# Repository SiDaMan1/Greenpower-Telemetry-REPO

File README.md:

# Greenpower Telemetry

A live telemetry system built for the Greenpower race vehicle. Sensors on the car — speed, battery/motor voltage, current, temperature, motor & wheel RPM, IMU orientation and G-forces, GPS, ESC state, LoRa link quality — stream off the car in real time, get picked up by a base-station receiver, and show up on a public web dashboard within a fraction of a second. Every packet is also saved, so past runs and test sessions can be reviewed and exported later, not just watched live.

```
Vehicle (greenpower_sender) ──LoRa──▶ greenpower_receiver ──USB──▶ receiver_agent ──▶ telemetry_web (dashboard)
                             └─ESP-NOW──▶ steering_wheel_display
```

- **`greenpower_sender`** — firmware on the car itself, reads every sensor and transmits over both LoRa (long-range, to the pits) and ESP-NOW (short-range, straight to the steering wheel).
- **`greenpower_receiver`** — a base-station ESP32 that catches the LoRa packets and relays them over USB.
- **`receiver_agent`** — a small background app on a laptop plugged into the receiver. It watches for the device, asks before forwarding (nothing goes live without a person clicking "Yes"), and pushes packets to the dashboard.
- **`telemetry_web`** — the dashboard itself: live numbers and charts, GPS raceline on a real map, session history with CSV export, installable as a mobile app.
- **`steering_wheel_display`** — the driver's own live readout, wired straight into the car's ESP-NOW link, no dependency on the receiver/agent/internet chain at all.

---

## 🏁 Live Dashboard

**[ascteracingmonitor.com →](https://ascteracingmonitor.com/)**

Open it anytime to see whatever the car is currently transmitting — speed, power, temperatures, RPM, ESC status, IMU data, live GPS raceline on satellite imagery, and LoRa link quality, all updating several times a second. When nothing is actively forwarding it just shows offline, not stale numbers pretending to be current.

A few things worth knowing if you're using it, not just building it:
- **Time range toggle** (top of the page) — switch the live charts between 1/5/15/30 minutes or the whole session, not just a fixed short window.
- **Sessions tab** — every run gets grouped automatically and stays browsable afterward, with a one-click CSV export of the full packet history.
- **Multi tab** — overlay several metrics normalized onto one chart, useful for spotting correlations (e.g. current spikes vs. RPM dips).
- **Install it as an app** — on a phone, use your browser's "Add to Home Screen"/"Install" option for a full-screen, no-browser-chrome experience with its own icon.

## 📥 Get telemetry flowing to the dashboard

If you just need the car's data reaching the dashboard, you don't need this whole repo — only the **receiver agent**, running on whatever laptop the base-station receiver is plugged into.

1. Click the button above → downloads `GreenpowerAgentSetup.msi` (a real Windows installer, ~500 KB)
2. Run it and click through the setup wizard

No unzipping, no `.bat` files — it's a proper installer: Start Menu shortcut, entry in Add/Remove Programs (Settings → Apps → Installed apps → Uninstall), no admin rights needed (installs to your own user folder). It still installs its own dependencies, config is already baked in, and it registers itself to auto-start at login (plus a small tray icon so you can tell it's running). Requires [Node.js](https://nodejs.org) (LTS) already installed. After setup, day-to-day use is just: plug in the receiver, click **Yes** on the notification that pops up asking permission to forward. Unplug/replug always re-asks — it never silently starts forwarding on its own.

`.msi`, not the more common `.exe` — deliberate, not a typo. An earlier `.exe` build (Inno Setup) worked fine generally but got hard-blocked by Windows on Intune-managed/corporate devices (a Defender rule that specifically targets raw executables); an MSI sidesteps that since it isn't that kind of file. See `receiver_agent/CLAUDE.md` if you're curious about the full story.

The same download button also lives on the dashboard itself (top-right, desktop) for anyone who lands there first — it opens a short confirmation dialog first, since this is now a real installer someone's about to run, not an inert zip.

More detail, including what the consent prompt is actually protecting against: [`receiver_agent/README.md`](receiver_agent/README.md)

---

## Project map

| Folder | What it is |
|---|---|
| [`greenpower_sender`](greenpower_sender) | Firmware on the vehicle (ESP32-S3) — reads sensors, transmits over LoRa + ESP-NOW |
| [`greenpower_receiver`](greenpower_receiver) | Firmware on a base-station ESP32 — receives LoRa, relays JSON over USB serial |
| [`receiver_agent`](receiver_agent) | Node.js background agent (runs on a laptop) — watches for the receiver over USB, asks before forwarding, relays to the dashboard, tray icon |
| [`telemetry_web`](telemetry_web) | The dashboard itself (Node/Express + Postgres), deployed on Railway — live view, session history, mobile PWA |
| [`steering_wheel_display`](steering_wheel_display) | Firmware for the steering wheel's own live display (ESP-NOW receiver) |
| [`mock_sender`](mock_sender) | Fake sender for testing the display/dashboard without the real car |
| [`esc controller`](esc%20controller) | Firmware for the motor controller (ESP32 WROOM-32), talks to the sender over UART |

Each folder has its own `CLAUDE.md` with the real technical detail — hardware wiring, pinouts, protocol formats, known gotchas. This README is the map for a human reader; those files are the AI-assistant-facing equivalent, kept in sync with whatever's actually true in the code.

## Running your own copy

Every piece here is meant to work as a drop-in replacement for testing without the real car: `mock_sender` speaks the exact same LoRa/ESP-NOW packet formats as `greenpower_sender`, so a receiver or steering-wheel display can't tell the difference — and `telemetry_web` itself has a built-in **Test Mode** toggle (top of the dashboard) that feeds realistic sample data through the live charts with no hardware at all, for trying out the UI. See each folder's own README/CLAUDE.md for the specifics of setting that piece up.

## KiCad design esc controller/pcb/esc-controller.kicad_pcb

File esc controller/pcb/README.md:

# ESC Controller PCB — rev D

A carrier board for the `throttle_controller` sketch. The ESP32 DevKit V1 (30-pin)
plugs into two female header strips. The SSD1306 OLED solders **flush to the board**
through four plated holes. Everything else leaves the board on **1 × 2 mm solder
pads** for flying leads.

**One component on the whole board: R1, a 4k7 pull-down on the ESC signal.**

Open `esc-controller.kicad_pro` in KiCad 7 or newer.

```
Board        73 × 60 mm, 2 layer, 1.6 mm
Copper       1 oz, GND pour both sides
Tracks       0.25 mm signal / 0.5 mm power
Vias         0.8 mm pad / 0.4 mm drill
Min clear.   0.3 mm  (well inside every cheap fab's limits)
DRC          0 violations, 0 unconnected pads, 0 footprint errors
```

### What changed from rev C

Area-optimised: **98 × 62 mm → 73 × 60 mm**, a 28% smaller board (6076 → 4380 mm²)
and 25 mm narrower. Nothing electrical changed — same nets, same pads, same parts.

- Three tight columns instead of loose ones: wire pads at the left edge, the
  DevKit socket, then the OLED with the UART pads tucked into the dead space
  underneath it
- **R1 now stands vertically** (2.54 mm pitch, one lead bent down) so it fits the
  3 mm lane between the pad labels and the socket. Same 4k7 resistor, just mounted
  on end — bend one lead back alongside the body before you fit it
- 5V IN moved to the left column, next to the VIN pin it feeds
- Smaller silkscreen text and tighter pad-group spacing throughout
- The two modules now take up 51% of the board area; the rest is wire pads,
  mounting holes and edge margin

### What changed from rev B

- ECO and SPORT are no longer two separate 2-pad groups. They're now **one 3-pad
  MODE SW group** — `ECO / COM / SPORT` — for a single 3-position switch
- Connectors renumbered again: TRIGGER is **J5**, UART OUT is **J6**, 5V IN is **J7**

### What changed from rev A

- All pull-ups, filter caps, bulk cap, power LED and its resistor removed
- R1 (4k7) rewired from series to a **pull-down**, ESC signal to ground
- OLED changed to four plated holes for flush mounting
- Board grew 95 → 98 mm wide

---

## The mode switch

`MODE SW` (J4) takes one **SP3T / 3-position** switch. Wire the switch's common
terminal — the centre pin on almost every slide switch — to the middle pad, and the
two outer terminals to `ECO` and `SPORT`. Because GND sits between the two signals,
the switch's three pins map straight across without any wire crossing over another.

| Switch position | ECO pin | SPORT pin | Mode |
|---|---|---|---|
| One end | pulled low | high | ECO |
| **Centre** | high | high | **NORMAL** |
| Other end | high | pulled low | SPORT |

That falls out of the firmware as written: both inputs are active-low, and with
neither pulled down it lands on NORMAL. There's no way for both to be low at once
with a single switch, so the "ECO wins if both are low" tie-break in the sketch
simply never fires — harmless to leave in.

Which end gives you ECO and which gives SPORT is just which way round you solder
the two outer wires. Swap them if it ends up backwards.

---

## What R1 does

GPIO25 goes straight to the `ESC OUT / SIG` pad. R1 sits across that signal to
ground.

The ESP32's pins are high-impedance during reset and for the first moments of
boot — nothing is driving them. Without a pull-down, the ESC input floats during
that window and can read as anything, which is how a car twitches or lurches when
you power it up. R1 holds the line at 0 V until the firmware takes over. It also
holds the ESC off if the signal wire ever comes loose.

At 3.3 V it draws 0.7 mA when GPIO25 is high — nothing next to what the pin can
source, and negligible against the 31 kHz switching.

**One thing to watch:** if your ESC's signal input has its own internal pull-up,
R1 forms a voltage divider with it and the idle level won't reach 0 V. If the
throttle won't fully close, or the ESC sees a standing signal with the ESP32
unplugged, that's the cause — swap R1 for 10 kΩ or higher. The pads take any
value; it's a one-part change, no board revision needed.

---

## ⚠️ Two things to check before you order

**1. The DevKit row pitch.** The socket assumes **25.4 mm (1.0") between the two
pin rows** — standard for a 30-pin DOIT DevKit V1, but some clones are 22.86 mm
(0.9"). Measure yours, centre-of-pin to centre-of-pin across the rows. If it's
different, change `ROW_SPACING` in `generator/design.py` and re-run
`generator/build.py`. Nothing else has to change.

**2. Where the OLED's pin row sits.** The four holes are on 2.54 mm pitch — that
part is universal. I've placed them **centred on the top edge** of the module and
drawn a 27.3 × 27.8 mm body outline on the silkscreen as a guide. If your module's
header is offset rather than centred, the module will just sit a few mm off from
the printed outline — the board area underneath is completely clear, so nothing
collides. Cosmetic only.

Pin order is **GND, VCC, SCL, SDA** left to right, viewed from above with the
screen facing up. Every hole is labelled on the silkscreen — check them against
your module before you solder, because getting GND and VCC swapped will kill the
display.

---

## Wiring — what goes on which pad

All solder pads are on the top layer, labelled on the silkscreen.

### Left edge

| Group | Pad | Net | Connect to | ESP32 |
|---|---|---|---|---|
| **POT** (J2) | 3V3 | +3V3 | pot terminal 1 | — |
| | WIPER | POT_W | pot wiper | GPIO34 |
| | GND | GND | pot terminal 3 | — |
| **ESC OUT** (J3) | SIG | ESC_SIG | ESC signal wire | GPIO25 direct, R1 pulls it down |
| | GND | GND | ESC ground | — |
| **MODE SW** (J4) | ECO | ECO | switch outer terminal | GPIO27 |
| | COM | GND | switch **common** (centre pin) | — |
| | SPORT | SPORT | switch other outer terminal | GPIO14 |
| **TRIGGER** (J5) | SW | TRIG | trigger switch, one side | GPIO13 |
| | GND | GND | trigger switch, other side | — |
| **5V IN** (J7) | 5V | +5V | BEC / buck output — **optional** | VIN |
| | GND | GND | BEC ground | — |

The trigger and both mode inputs are active-low and rely on the **ESP32's internal
pull-ups** — make sure the sketch declares these pins as `INPUT_PULLUP`, not plain
`INPUT`, or they'll float.

### Right side and OLED

| Group | Pad | Net | Connect to | ESP32 |
|---|---|---|---|---|
| **OLED** (J1) | GND, VCC, SCL, SDA | — | module solders flush, pins down | GPIO22 = SCL, GPIO21 = SDA |
| **UART OUT** (J6, under the OLED) | TX | UART_TX | display_receiver RX | GPIO17 |
| | RX | UART_RX | display_receiver TX | GPIO16 |
| | GND | GND | display_receiver GND | — |

**J7 is optional.** You're on USB power, so leave it unpopulated. It's there so the
board can run standalone later without a redesign. If you do use it, **don't leave
USB plugged in at the same time** — the DevKit V1 has no isolation between the USB
5V rail and VIN.

---

## Bill of materials

| Ref | Value | Package | Qty | Notes |
|---|---|---|---|---|
| U1 | 1×15 female header, 2.54 mm | THT | 2 | Cut from a 40-pin strip. The DevKit sits in these. |
| R1 | 4.7 kΩ | axial, **mounted vertically**, 2.54 mm | 1 | Pull-down, ESC signal to GND |
| H1–H4 | M3 | 3.2 mm hole | 4 | Mounting |

That's the entire BOM. J1 is four plated holes — the OLED module's own pins go
through them, no header needed. J2–J7 are bare solder pads. The mode switch,
trigger, pot and ESC are all off-board on flying leads.

---

## Assembly order

1. **R1** first. It mounts **standing up**: bend one lead 180° back along the body
   so both leads come out of the same end, 2.54 mm apart. Either way round; a
   resistor isn't polarised.
2. **The two 1×15 female strips for U1.** Plug the DevKit into them while you
   solder so the rows end up parallel, but keep it unpowered.
3. **The OLED.** Its pin header goes through J1 from the top with the module lying
   flat on the board; solder underneath and trim the pins flush. Check the four
   silkscreen labels against the module first.
4. **Flying leads** to the solder pads. Tin the pad, tin the wire, lay the wire flat
   on the pad and reflow. Add a dab of hot glue after testing — an unsupported
   soldered wire will fatigue and snap in a race car.

The OLED sits directly on the board, so the copper under it is bare board and
solder mask only — no components, nothing to short against.

---

## Manufacturing

`gerbers.zip` uploads to JLCPCB / PCBWay / OSHPark as-is (Gerber X2 + Excellon
drill, mm). Default settings: 2 layer, 1.6 mm, HASL, any colour. At 73 × 60 mm
it's comfortably inside the 100 × 100 mm price break — roughly $2–5 for five
boards plus shipping.

### If you need it smaller still

Two things set the size, and both are choices rather than physics:

- **The four M3 mounting holes** cost roughly 7 mm of board at each corner. Two
  holes instead of four, or M2.5 instead of M3, would let the board come in
  another 4–5 mm each way.
- **The layout is three columns.** Stacking the OLED *below* the DevKit instead
  of beside it gives a long, narrow board (about 45 × 85 mm) — slightly less area,
  but a much less square shape. Better if it mounts along a dash rail, worse if
  it goes in a box.

Say which you'd prefer and it's a placement change in `design.py`, not a redesign.

---

## Regenerating

The project is generated from source, so changes stay consistent:

```
cd generator
python3 build.py      # places, routes, checks clearances, writes the .kicad_pcb
python3 gen_sch.py    # writes the .kicad_sch and .kicad_pro
```

`design.py` holds everything worth changing — board size, `ROW_SPACING`, placement,
the pad groups and the netlist. `router.py` is a two-layer maze router with
clearance checking; `build.py` places, routes, then runs its own geometric
clearance and connectivity checks before writing the board. Needs `numpy`.

---

## Verification done on this design

- KiCad's own DRC: **0 violations, 0 unconnected pads, 0 footprint errors**
  (see `drc_report.txt`)
- Independent geometric clearance check: 0 pairs closer than 0.20 mm
- Independent connectivity check: every net's pads joined by copper
- Schematic netlist exported and diffed against the PCB netlist — **all 12 nets
  match exactly**, same pads on the same nets, same footprints
- `ECO` confirmed as J4 pad 1 → U1 pin 10 (GPIO27), `SPORT` as J4 pad 3 → U1
  pin 11 (GPIO14), and J4 pad 2 on GND
- `ESC_SIG` confirmed to carry exactly U1 pin 8 (GPIO25), J3 pad 1 and R1 pad 1,
  with R1 pad 2 landing in the ground pour
- Every GPIO cross-checked against `SYSTEM_INFO.md`, and every pin confirmed to
  exist on the 30-pin DevKit V1
- Thermal relief checked: every ground through-hole pad gets at least two spokes
  into the pour, so no pad hangs off the plane by a single thin bridge

The two things software can't check for you are the 25.4 mm row pitch and your
OLED's pin order. Both are one measurement each.

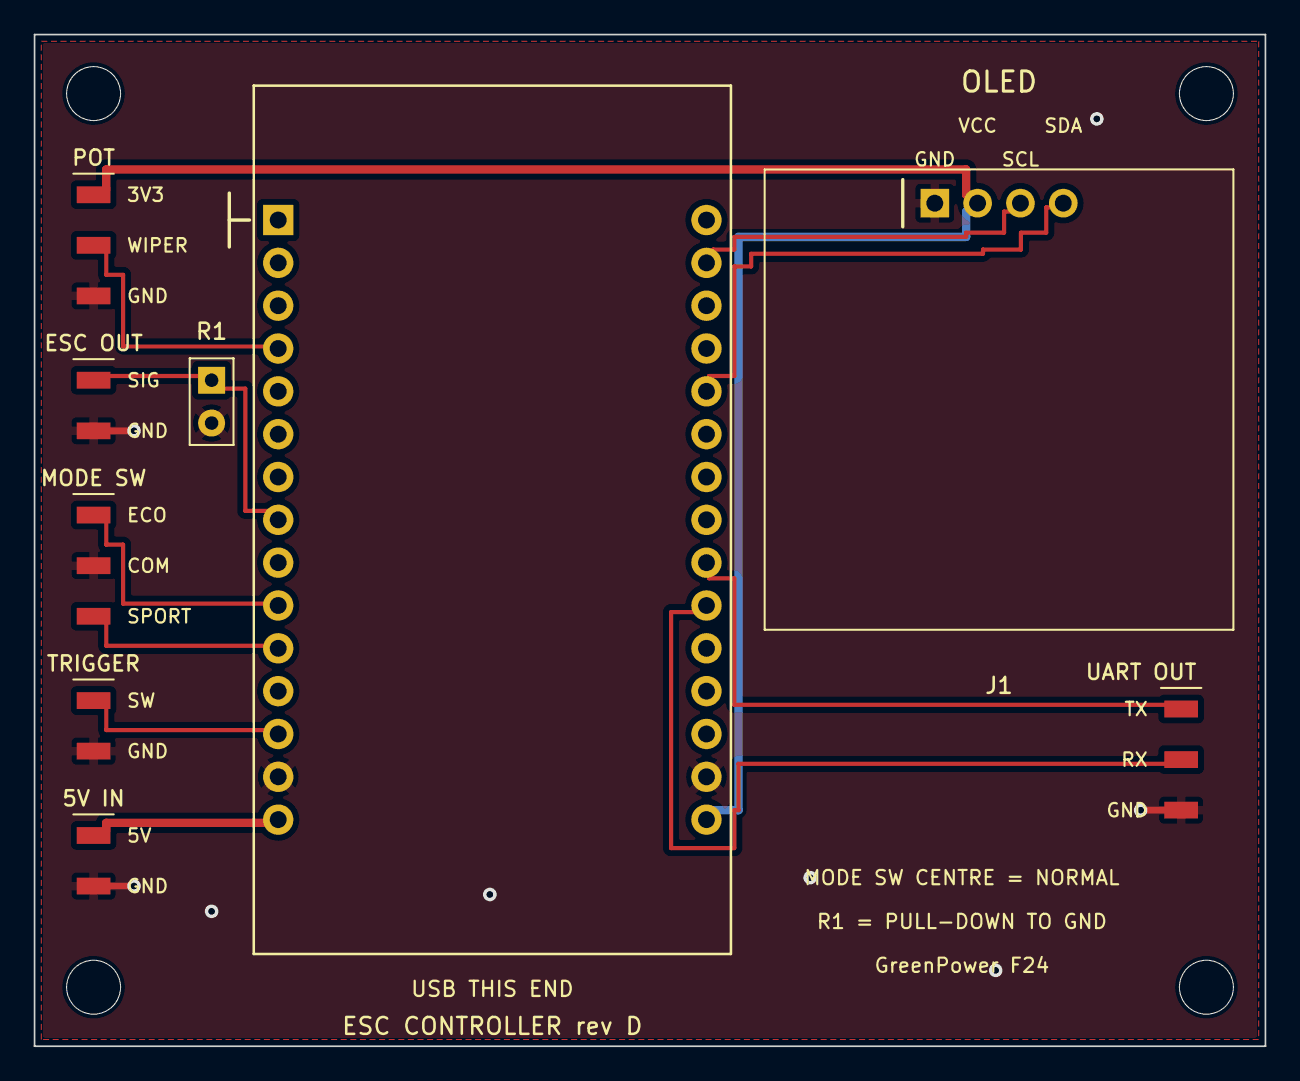
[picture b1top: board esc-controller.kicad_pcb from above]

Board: 2 copper layers, 73.0 x 60.0 mm, 13 parts (0 on the bottom side), 12 nets.

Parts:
H1, H2, H3, H4: MountingHole_M3; MountingHole_3.2mm_M3
J1: SSD1306_0.96in; OLED_SSD1306_096_FLUSH_1x4
J2: WirePads; SOLDERPAD_POT_3P
J3: WirePads; SOLDERPAD_ESC_OUT_2P
J4: WirePads; SOLDERPAD_MODE_SW_3P
J5: WirePads; SOLDERPAD_TRIGGER_2P
J6: WirePads; SOLDERPAD_UART_OUT_3P
J7: WirePads; SOLDERPAD_5V_IN_2P
R1: 4k7; Resistor_THT_Axial_P2.54mm_Vertical
U1: ESP32-DevKitV1-30p; ESP32_DEVKITV1_30P_SOCKET

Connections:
+3V3: J1.2, J2.1, U1.30
+5V: J7.1, U1.15
ECO: J4.1, U1.10
ESC_SIG: J3.1, R1.1, U1.8
GND: J1.1, J2.3, J3.2, J4.2, J5.2, J6.3, J7.2, R1.2, U1.14, U1.29
POT_W: J2.2, U1.4
SCL: J1.3, U1.17
SDA: J1.4, U1.20
SPORT: J4.3, U1.11
TRIG: J5.1, U1.13
UART_RX: J6.2, U1.25
UART_TX: J6.1, U1.24

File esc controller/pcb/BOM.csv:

Ref,Value,Footprint,Qty,Description
U1,1x15 female header 2.54mm,esc:ESP32_DEVKITV1_30P_SOCKET,2,Socket strips for ESP32 DevKit V1 30-pin (cut from 40-pin strip)
R1,4k7,esc:Resistor_THT_Axial_P2.54mm_Vertical,1,Pull-down from ESC signal to GND - MOUNTED VERTICALLY (bend one lead back along the body)
H1-H4,M3,esc:MountingHole_3.2mm_M3,4,Mounting holes
J1,OLED holes,esc:OLED_SSD1306_096_FLUSH_1x4,1,4 plated holes 2.54mm - SSD1306 solders flush - GND VCC SCL SDA
J2,POT pads,esc:SOLDERPAD_POT_3P,1,Solder pads 1x2mm: 3V3 / WIPER / GND
J3,ESC OUT pads,esc:SOLDERPAD_ESC_OUT_2P,1,Solder pads 1x2mm: SIG / GND
J4,MODE SW pads,esc:SOLDERPAD_MODE_SW_3P,1,Solder pads 1x2mm: ECO / COM / SPORT - one 3-position switch, common to COM
J5,TRIGGER pads,esc:SOLDERPAD_TRIGGER_2P,1,Solder pads 1x2mm: SW / GND
J6,UART OUT pads,esc:SOLDERPAD_UART_OUT_3P,1,Solder pads 1x2mm: TX / RX / GND
J7,5V IN pads,esc:SOLDERPAD_5V_IN_2P,1,Solder pads 1x2mm: 5V / GND - OPTIONAL do not fit for USB power

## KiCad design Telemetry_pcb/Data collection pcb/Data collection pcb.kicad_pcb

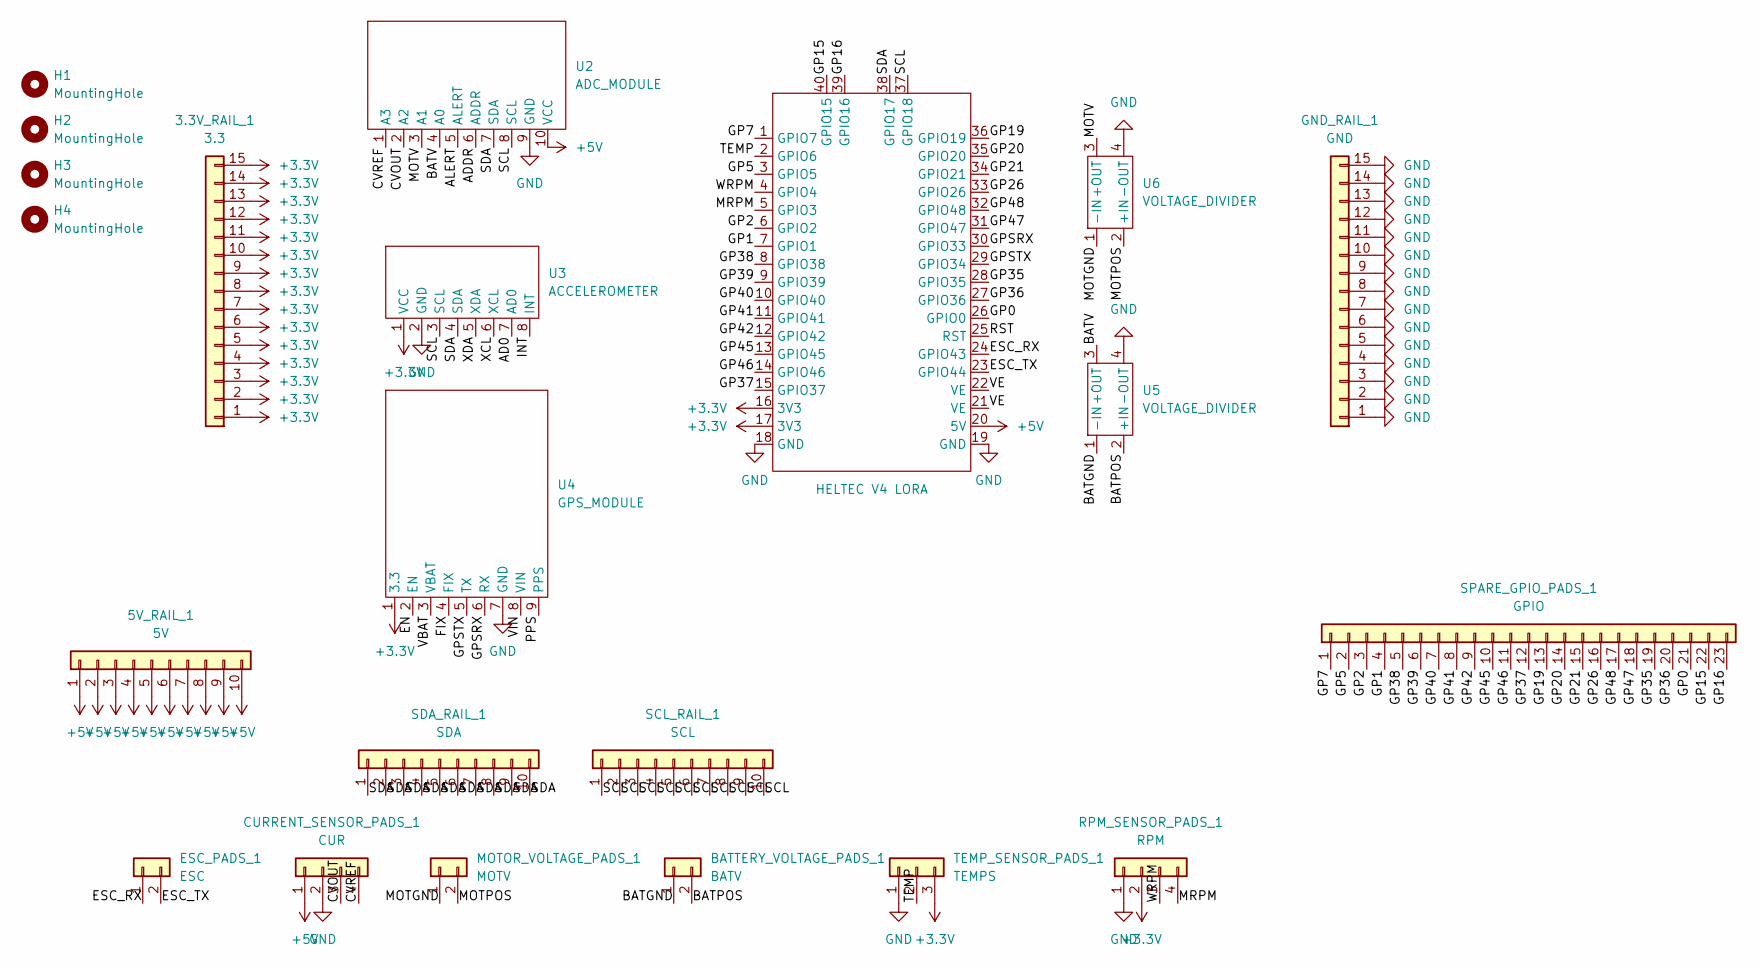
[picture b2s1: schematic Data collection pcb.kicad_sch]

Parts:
3.3V_RAIL_1: 3.3; 1X15 PADS
5V_RAIL_1: 5V; 1X10 PADS
BATTERY_VOLTAGE_PADS_1: BATV; 1X02 PADS
CURRENT_SENSOR_PADS_1: CUR; 1X04 PADS
ESC_PADS_1: ESC; 1X02 PADS
GND_RAIL_1: GND; 1X15 PADS
H1, H2, H3, H4: MountingHole; MountingHole_3.2mm_M3
MOTOR_VOLTAGE_PADS_1: MOTV; 1X02 PADS
RPM_SENSOR_PADS_1: RPM; 1X04 PADS
SCL_RAIL_1: SCL; 1X10 PADS
SDA_RAIL_1: SDA; 1X10 PADS
SPARE_GPIO_PADS_1: GPIO; 1X23 PADS
TEMP_SENSOR_PADS_1: TEMPS; 1X03 PADS
U1: HELTEC V4 LORA; HELTEC V4
U2: ADC_MODULE
U3: ACCELEROMETER
U4: GPS_MODULE
U5, U6: VOLTAGE_DIVIDER

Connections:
+3.3V: 3.3V_RAIL_1.1, 3.3V_RAIL_1.2, 3.3V_RAIL_1.3, 3.3V_RAIL_1.4, 3.3V_RAIL_1.5, 3.3V_RAIL_1.6, 3.3V_RAIL_1.7, 3.3V_RAIL_1.8, 3.3V_RAIL_1.9, 3.3V_RAIL_1.10, 3.3V_RAIL_1.11, 3.3V_RAIL_1.12, 3.3V_RAIL_1.13, 3.3V_RAIL_1.14, 3.3V_RAIL_1.15, RPM_SENSOR_PADS_1.2, TEMP_SENSOR_PADS_1.3, U1.16 (3V3), U1.17 (3V3), U3.1 (VCC), U4.1 (3.3); also elsewhere on the board
+5V: 5V_RAIL_1.1, 5V_RAIL_1.2, 5V_RAIL_1.3, 5V_RAIL_1.4, 5V_RAIL_1.5, 5V_RAIL_1.6, 5V_RAIL_1.7, 5V_RAIL_1.8, 5V_RAIL_1.9, 5V_RAIL_1.10, CURRENT_SENSOR_PADS_1.1, U1.20 (5V), U2.10 (VCC)
/AD0: U3.7 (AD0)
/ADDR: U2.6 (ADDR)
/ALERT: U2.5 (ALERT)
/BATGND: BATTERY_VOLTAGE_PADS_1.1, U5.1 (-IN)
/BATPOS: BATTERY_VOLTAGE_PADS_1.2, U5.2 (+IN)
/BATV: U2.4 (A0), U5.3 (+OUT)
/CVOUT: CURRENT_SENSOR_PADS_1.3, U2.2 (A2)
/CVREF: CURRENT_SENSOR_PADS_1.4, U2.1 (A3)
/EN: U4.2 (EN)
/ESC_RX: ESC_PADS_1.1, U1.24 (GPIO43)
/ESC_TX: ESC_PADS_1.2, U1.23 (GPIO44)
/FIX: U4.4 (FIX)
/GP0: SPARE_GPIO_PADS_1.21, U1.26 (GPIO0)
/GP1: SPARE_GPIO_PADS_1.4, U1.7 (GPIO1)
/GP2: SPARE_GPIO_PADS_1.3, U1.6 (GPIO2)
/GP5: SPARE_GPIO_PADS_1.2, U1.3 (GPIO5); also elsewhere on the board
/GP7: SPARE_GPIO_PADS_1.1, U1.1 (GPIO7); also elsewhere on the board
/GP15: SPARE_GPIO_PADS_1.22, U1.40 (GPIO15)
/GP16: SPARE_GPIO_PADS_1.23, U1.39 (GPIO16)
/GP19: SPARE_GPIO_PADS_1.13, U1.36 (GPIO19)
/GP20: SPARE_GPIO_PADS_1.14, U1.35 (GPIO20)
/GP21: SPARE_GPIO_PADS_1.15, U1.34 (GPIO21)
/GP26: SPARE_GPIO_PADS_1.16, U1.33 (GPIO26)
/GP35: SPARE_GPIO_PADS_1.19, U1.28 (GPIO35)
/GP36: SPARE_GPIO_PADS_1.20, U1.27 (GPIO36)
/GP37: SPARE_GPIO_PADS_1.12, U1.15 (GPIO37)
/GP38: SPARE_GPIO_PADS_1.5, U1.8 (GPIO38)
/GP39: SPARE_GPIO_PADS_1.6, U1.9 (GPIO39)
/GP40: SPARE_GPIO_PADS_1.7, U1.10 (GPIO40)
/GP41: SPARE_GPIO_PADS_1.8, U1.11 (GPIO41)
/GP42: SPARE_GPIO_PADS_1.9, U1.12 (GPIO42)
/GP45: SPARE_GPIO_PADS_1.10, U1.13 (GPIO45)
/GP46: SPARE_GPIO_PADS_1.11, U1.14 (GPIO46)
/GP47: SPARE_GPIO_PADS_1.18, U1.31 (GPIO47); also elsewhere on the board
/GP48: SPARE_GPIO_PADS_1.17, U1.32 (GPIO48); also elsewhere on the board
/GPSRX: U1.30 (GPIO33), U4.6 (RX)
/GPSTX: U1.29 (GPIO34), U4.5 (TX)
/INT: U3.8 (INT)
/MOTGND: MOTOR_VOLTAGE_PADS_1.1, U6.1 (-IN)
/MOTPOS: MOTOR_VOLTAGE_PADS_1.2, U6.2 (+IN)
/MOTV: U2.3 (A1), U6.3 (+OUT)
/MRPM: RPM_SENSOR_PADS_1.4, U1.5 (GPIO3)
/PPS: U4.9 (PPS)
/RST: U1.25 (RST)
/SCL: SCL_RAIL_1.1, SCL_RAIL_1.2, SCL_RAIL_1.3, SCL_RAIL_1.4, SCL_RAIL_1.5, SCL_RAIL_1.6, SCL_RAIL_1.7, SCL_RAIL_1.8, SCL_RAIL_1.9, SCL_RAIL_1.10, U1.37 (GPIO18), U2.8 (SCL), U3.3 (SCL); also elsewhere on the board
/SDA: SDA_RAIL_1.1, SDA_RAIL_1.2, SDA_RAIL_1.3, SDA_RAIL_1.4, SDA_RAIL_1.5, SDA_RAIL_1.6, SDA_RAIL_1.7, SDA_RAIL_1.8, SDA_RAIL_1.9, SDA_RAIL_1.10, U1.38 (GPIO17), U2.7 (SDA), U3.4 (SDA); also elsewhere on the board
/TEMP: TEMP_SENSOR_PADS_1.2, U1.2 (GPIO6)
/VBAT: U4.3 (VBAT)
/VE: U1.21 (VE), U1.22 (VE)
/VIN: U4.8 (VIN)
/WRPM: RPM_SENSOR_PADS_1.3, U1.4 (GPIO4)
/XCL: U3.6 (XCL)
/XDA: U3.5 (XDA)
GND: CURRENT_SENSOR_PADS_1.2, GND_RAIL_1.1, GND_RAIL_1.2, GND_RAIL_1.3, GND_RAIL_1.4, GND_RAIL_1.5, GND_RAIL_1.6, GND_RAIL_1.7, GND_RAIL_1.8, GND_RAIL_1.9, GND_RAIL_1.10, GND_RAIL_1.11, GND_RAIL_1.12, GND_RAIL_1.13, GND_RAIL_1.14, GND_RAIL_1.15, RPM_SENSOR_PADS_1.1, TEMP_SENSOR_PADS_1.1, U1.18 (GND), U1.19 (GND), U2.9 (GND), U3.2 (GND), U4.7 (GND), U5.4 (-OUT), U6.4 (-OUT); also elsewhere on the board

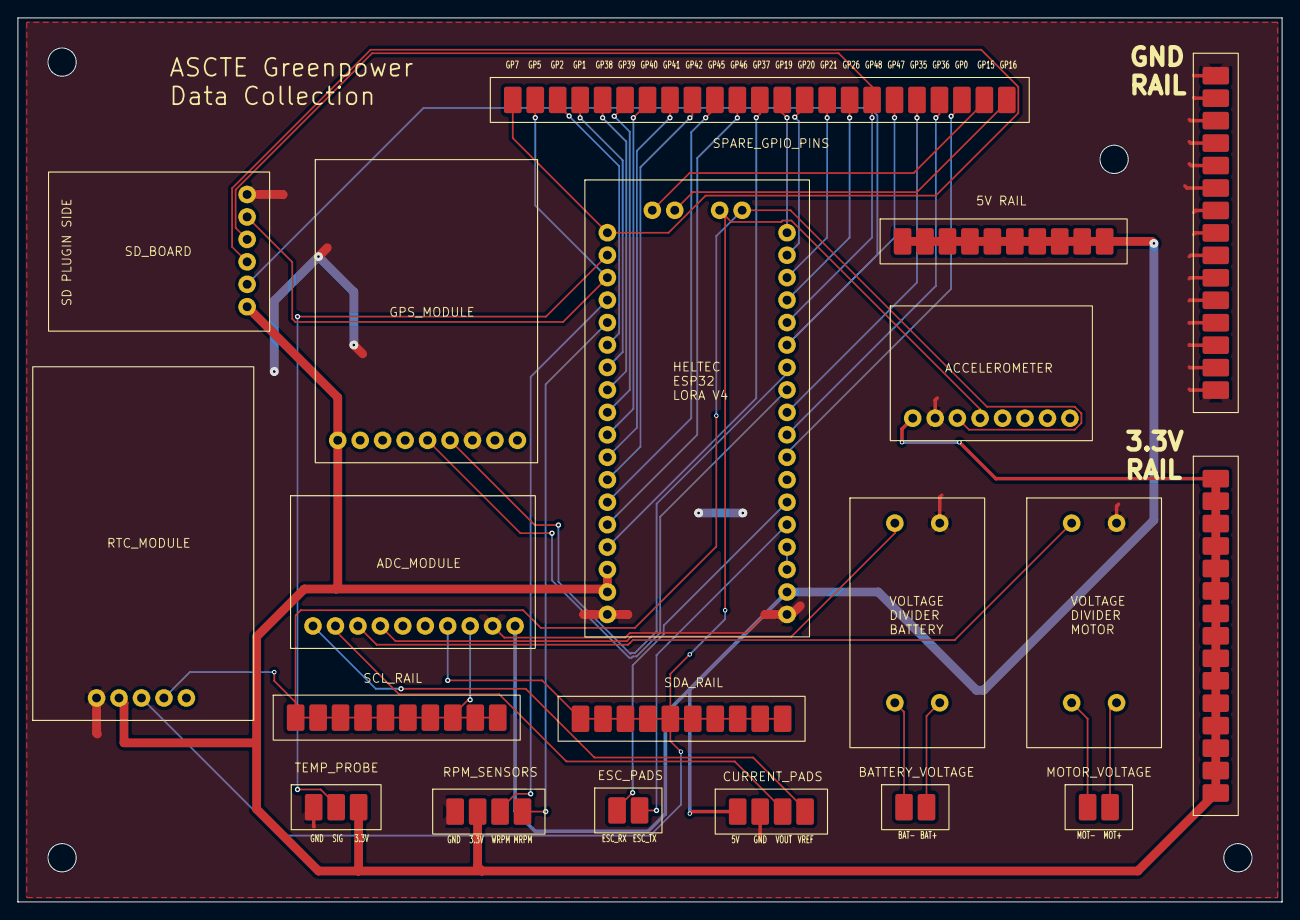
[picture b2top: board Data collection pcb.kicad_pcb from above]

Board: 2 copper layers, 143.0 x 100.0 mm, 24 parts (0 on the bottom side), 44 nets.

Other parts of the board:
U7: SD_BOARD
U8: RTC_MODULE

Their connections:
+3.3V: U7.6 (3.3V), U8.4 (3.3V); also elsewhere on the board
/GP5: U7.2 (MISO); also elsewhere on the board
/GP7: U7.4 (MOSI); also elsewhere on the board
/GP47: U7.5 (CS); also elsewhere on the board
/GP48: U7.3 (CLK); also elsewhere on the board
/SCL: U8.2 (SCL); also elsewhere on the board
/SDA: U8.3 (SDA); also elsewhere on the board
GND: U7.1 (GND), U8.5 (GND); also elsewhere on the board

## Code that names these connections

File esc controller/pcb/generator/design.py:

"""
Design database for the ESC Controller PCB -- rev D (area-optimised).

Board: 73 x 60 mm, 2 layer.
  - ESP32 DevKit V1 (30-pin DOIT) sits in 2x15 female headers
  - SSD1306 0.96" OLED solders flush to the board through 4 plated holes
  - everything else leaves the board on 1 x 2 mm solder pads
  - one component only: R1, 4k7 pull-down on the ESC signal (holds the
    ESC input low while the ESP32 is in reset / booting)

Coordinates in mm, KiCad convention (origin top-left, Y down).
"""

BOARD_W = 73.0
BOARD_H = 60.0

NETS = [
    "",            # 0
    "GND",         # 1
    "+3V3",        # 2
    "+5V",         # 3
    "POT_W",       # 4
    "ESC_SIG",     # 5
    "TRIG",        # 6
    "ECO",         # 7
    "SPORT",       # 8
    "SDA",         # 9
    "SCL",         # 10
    "UART_TX",     # 11
    "UART_RX",     # 12
]
NETID = {n: i for i, n in enumerate(NETS)}

# ---------------------------------------------------------------- footprints
# Each component: ref, value, fp (footprint name), at (x,y), pads[]
# pad: (number, kind, shape, (lx,ly), (w,h), drill, net, name)
#   kind: 'tht' | 'smd' | 'npth'

WIREPAD = (2.0, 1.0)      # 1mm x 2mm solder pad for wires (long axis outward)

ESP32_PINS = [
    # (pin, name, net)
    (1,  "EN",     ""),
    (2,  "GPIO36", ""),
    (3,  "GPIO39", ""),
    (4,  "GPIO34", "POT_W"),
    (5,  "GPIO35", ""),
    (6,  "GPIO32", ""),
    (7,  "GPIO33", ""),
    (8,  "GPIO25", "ESC_SIG"),
    (9,  "GPIO26", ""),
    (10, "GPIO27", "ECO"),
    (11, "GPIO14", "SPORT"),
    (12, "GPIO12", ""),
    (13, "GPIO13", "TRIG"),
    (14, "GND",    "GND"),
    (15, "VIN",    "+5V"),
    (16, "GPIO23", ""),
    (17, "GPIO22", "SCL"),
    (18, "TX0",    ""),
    (19, "RX0",    ""),
    (20, "GPIO21", "SDA"),
    (21, "GPIO19", ""),
    (22, "GPIO18", ""),
    (23, "GPIO5",  ""),
    (24, "GPIO17", "UART_TX"),
    (25, "GPIO16", "UART_RX"),
    (26, "GPIO4",  ""),
    (27, "GPIO2",  ""),
    (28, "GPIO15", ""),
    (29, "GND",    "GND"),
    (30, "3V3",    "+3V3"),
]

ROW_SPACING = 25.4        # <-- measure your board! 1.0" is standard DOIT V1 30-pin
PIN_PITCH = 2.54


def esp32_socket(at):
    pads = []
    for pin, name, net in ESP32_PINS:
        if pin <= 15:
            lx, ly = 0.0, (pin - 1) * PIN_PITCH
        else:
            lx, ly = ROW_SPACING, (pin - 16) * PIN_PITCH
        shape = "rect" if pin == 1 else "circle"
        pads.append((str(pin), "tht", shape, (lx, ly), (1.8, 1.8), 1.0, net, name))
    return dict(ref="U1", value="ESP32-DevKitV1-30p",
                fp="ESP32_DEVKITV1_30P_SOCKET", at=at, pads=pads,
                body=(-1.45, -7.97, 26.85, 43.53),   # module outline, local
                desc="2x15 female header, 2.54mm pitch, 25.4mm rows")


def wirepads(ref, at, entries, desc):
    """entries: list of (net, label). Pads stack downward at 3mm pitch."""
    pads = []
    for i, (net, label) in enumerate(entries):
        pads.append((str(i + 1), "smd", "rect", (0.0, i * 3.0), WIREPAD, None, net, label))
    return dict(ref=ref, value="WirePads", fp="SOLDERPAD_1x2MM_%dP" % len(entries),
                at=at, pads=pads, desc=desc)


def header1x(ref, value, at, entries, desc, horiz=False, fp=None):
    pads = []
    for i, (net, label) in enumerate(entries):
        shape = "rect" if i == 0 else "circle"
        loc = (i * 2.54, 0.0) if horiz else (0.0, i * 2.54)
        pads.append((str(i + 1), "tht", shape, loc, (1.7, 1.7), 1.0, net, label))
    return dict(ref=ref, value=value,
                fp=fp or ("PinHeader_1x%02d_P2.54mm_Vertical" % len(entries)),
                at=at, pads=pads, desc=desc, horiz=horiz)


def axial(ref, value, at, pitch, n1, n2, fp, pad=1.6, drill=0.8, vert=False):
    p2 = (0.0, pitch) if vert else (pitch, 0.0)
    pads = [("1", "tht", "rect", (0.0, 0.0), (pad, pad), drill, n1, ""),
            ("2", "tht", "circle", p2, (pad, pad), drill, n2, "")]
    return dict(ref=ref, value=value, fp=fp, at=at, pads=pads, pitch=pitch)


def mount(ref, at):
    return dict(ref=ref, value="MountingHole_M3", fp="MountingHole_3.2mm_M3",
                at=at, pads=[("", "npth", "circle", (0.0, 0.0), (3.2, 3.2), 3.2, "", "")])


def _lbl(comp, text):
    comp["label"] = text
    return comp


# ---------------------------------------------------------------- placement
# Three columns, packed tight:
#   A  x 2.5-8    wire pads + labels, all the off-board wiring except UART
#   B  x 13-41.3  the ESP32 DevKit, USB pointing at the bottom edge
#   C  x 43.3-71  the OLED on top, UART pads in the space underneath it
# R1 stands vertically in the 3mm lane between columns A and B.
COMPONENTS = []

# --- ESP32 socket -----------------------------------------------------------
COMPONENTS.append(esp32_socket((14.45, 11.0)))     # body spans x 13.0-41.3

# --- COLUMN A: wire pads, ordered to match the DevKit's left pin row so no
#     two signal traces have to cross on the way in
COMPONENTS.append(_lbl(wirepads("J2", (3.5, 9.5),
                               [("+3V3", "3V3"), ("POT_W", "WIPER"), ("GND", "GND")],
                               "Throttle potentiometer"), "POT"))
COMPONENTS.append(_lbl(wirepads("J3", (3.5, 20.5),
                               [("ESC_SIG", "SIG"), ("GND", "GND")],
                               "ESC signal output - direct from GPIO25, R1 pulls it down"),
                       "ESC OUT"))
COMPONENTS.append(_lbl(wirepads("J4", (3.5, 28.5),
                               [("ECO", "ECO"), ("GND", "COM"), ("SPORT", "SPORT")],
                               "3-position mode switch: ECO / centre=NORMAL / SPORT"),
                       "MODE SW"))
COMPONENTS.append(_lbl(wirepads("J5", (3.5, 39.5),
                               [("TRIG", "SW"), ("GND", "GND")],
                               "Trigger / throttle button"), "TRIGGER"))
COMPONENTS.append(_lbl(wirepads("J7", (3.5, 47.5),
                               [("+5V", "5V"), ("GND", "GND")],
                               "OPTIONAL 5V input (BEC) - leave open when USB powered"),
                       "5V IN"))

# --- the only component, stood on end to save board -------------------------
# R1 sits across the ESC signal to ground. GPIO25 is high-impedance during
# reset and boot, so without this the ESC input floats and the car can twitch
# at power-on. Pad 2 lands in the ground pour.
COMPONENTS.append(axial("R1", "4k7", (10.5, 20.5), 2.54, "ESC_SIG", "GND",
                        "Resistor_THT_Axial_P2.54mm_Vertical", vert=True))

# --- COLUMN C: OLED on four plated holes, module solders flush --------------
_j1 = header1x("J1", "SSD1306_0.96in", (53.39, 10.0),
               [("GND", "GND"), ("+3V3", "VCC"), ("SCL", "SCL"), ("SDA", "SDA")],
               "SSD1306 OLED - solder module flush, pins through board",
               horiz=True, fp="OLED_SSD1306_096_FLUSH_1x4")
_j1["silk_box"] = (-10.09, -2.0, 17.71, 25.3)    # 27.3 x 27.8 mm module body
COMPONENTS.append(_j1)

# UART pads live in the dead space under the OLED, at the right edge
COMPONENTS.append(_lbl(wirepads("J6", (68.0, 40.0),
                               [("UART_TX", "TX"), ("UART_RX", "RX"), ("GND", "GND")],
                               "UART to display_receiver"), "UART OUT"))

# --- mounting holes, tucked into the four corners ---------------------------
for _i, (_x, _y) in enumerate([(3.5, 3.5), (69.5, 3.5), (3.5, 56.5), (69.5, 56.5)]):
    COMPONENTS.append(mount("H%d" % (_i + 1), (_x, _y)))


# ---------------------------------------------------------------- silkscreen
SILK = [
    # (text, x, y, size, rot, layer)
    ("USB THIS END", 27.15, 56.6, 0.9, 0, "F.SilkS"),
    ("ESC CONTROLLER rev D", 27.15, 58.8, 1.0, 0, "F.SilkS"),
    ("MODE SW CENTRE = NORMAL", 55.0, 50.0, 0.85, 0, "F.SilkS"),
    ("R1 = PULL-DOWN TO GND", 55.0, 52.6, 0.85, 0, "F.SilkS"),
    ("GreenPower F24", 55.0, 55.2, 0.85, 0, "F.SilkS"),
]

# reference-designator placement, local to each footprint origin:
#   (dx, dy, justify)  --  justify None = centred
REFPOS = {
    "J1": (3.81, 28.6, None),
    "R1": (0.0, -2.9, None),
}
# refs that carry no assembly meaning go on F.Fab so the silkscreen stays clean
REF_ON_FAB = {"U1", "J2", "J3", "J4", "J5", "J6", "J7",
              "H1", "H2", "H3", "H4"}

# extra ground-stitching vias, placed in open copper (any that do not fit are
# skipped automatically by build.py)
STITCH_VIAS = [(10.5, 6.5), (10.5, 52.0), (27.0, 6.5), (27.0, 51.0),
               (46.0, 40.0), (46.0, 50.0), (63.0, 5.0), (57.0, 55.5)]


# Give every wire-pad group its own footprint name: the silkscreen labels
# differ per group, so sharing one library footprint would mismatch.
import re as _re
for _c in COMPONENTS:
    if _c.get("label") and _c["fp"].startswith("SOLDERPAD"):
        _slug = _re.sub(r"[^A-Z0-9]+", "_", _c["label"].upper()).strip("_")
        _c["fp"] = "SOLDERPAD_%s_%dP" % (_slug, len(_c["pads"]))

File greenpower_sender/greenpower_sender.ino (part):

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//
//  Sensors collected (all point-to-point wiring, no PCB):
//    • GPS NMEA         — Adafruit Ultimate GPS Breakout V3, Serial1
//                          GPIO34 = ESP32 RX (from GPS TX)
//                          GPIO33 = ESP32 TX (to GPS RX)
//    • IMU              — HW-123 (MPU6050-compatible), I2C SDA=17/SCL=18
//    • Temp probe        — DS18B20, 1-Wire digital, GPIO6 (4.7k pull-up to VCC)
//    • ADS1115 (Lonely Binary board), I2C SDA=17/SCL=18, addr 0x48:
//         A0 = motorVolt   — via 5:1 divider (VCC<25V)
//         A1 = battVolt    — via 5:1 divider (VCC<25V)
//         A2 = Vout        — YHDC HSTS016L 100A current sensor output
//         A3 = Vref        — YHDC HSTS016L reference (measured, not assumed)
//    • Motor RPM         — laser-interrupt disc sensor, GPIO4 (CHANGE-edge, polarity-agnostic)
//    • Wheel RPM         — laser-interrupt disc sensor, GPIO3 (CHANGE-edge, polarity-agnostic)
//    • ESC controller    — UART (Serial2), GPIO44(RX)/GPIO43(TX), from
//                          ../esc controller/throttle_controller.ino (ESP32
//                          WROOM-32, TX=GPIO17/RX=GPIO16 on that end).
//                          20 Hz CSV: mode,state,setpointPct,livePct,rampPct
//    • SD card           — local telemetry backup, own SPI bus (separate
//                          from the LoRa radio's), CS=47 SCK=48 MOSI=7
//                          MISO=5. Logs every packet to /LOGnnn.CSV
//                          regardless of whether the LoRa link is up.
//    • RTC               — Elegoo DS1307-V03, own I2C bus (Wire1) on
//                          GPIO1(SDA)/GPIO2(SCL) — NOT the shared IMU/ADS1115
//                          bus (GPIO17/18), because the DS1307 is fixed at
//                          I2C address 0x68, same as the MPU6050-compatible
//                          IMU already on that bus. Stamps each SD log row
//                          with real wall-clock time instead of just millis().
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
#define TEMP_PROBE_PIN     6   // DS18B20 1-Wire data (needs 4.7k pull-up to VCC)

#define ESC_RX_PIN        44   // ESP32 RX  ← ESC controller TX (GPIO17 on that board)
#define ESC_TX_PIN        43   // ESP32 TX  → ESC controller RX (GPIO16 on that board) — unused by the ESC's code today, wired for symmetry
#define ESC_BAUD      115200   // must match throttle_controller.ino's Serial1.begin()

#define MOTOR_RPM_PIN      4   // laser-interrupt — motor disc (was wrongly 48 — never wired)
#define WHEEL_RPM_PIN      3   // laser-interrupt — wheel disc (was wrongly 47 — never wired)
                                // GPIO3 is a boot-strapping pin — fine as a normal input
                                // after boot, don't be alarmed by a reading that looks odd
                                // for an instant right at power-up.

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// specifically cross-checked against every other pin already in use on
// this board (GPS/I2C/temp/ESC/RPM above, plus the LoRa radio's own
// internal pins) before being chosen — see greenpower_sender/CLAUDE.md's
// SD-card rule for the full pin-conflict check. GPIO47/48 have no other
// function on this board at all; GPIO5/7 are touch/ADC1-capable but that
// doesn't stop them being used as plain digital SPI pins here.
#define SD_CS_PIN         47
#define SD_SCK_PIN        48
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#define SD_MISO_PIN        5

// ── RTC (Elegoo DS1307-V03) ──────────────────────────────────────────
// A SECOND, independent I2C bus — NOT the existing GPIO17/18 bus. The
// DS1307 has a fixed, non-configurable I2C address (0x68), which is the
// exact same address the MPU6050-compatible IMU already answers to on
// that bus — putting both on one bus means one of them silently doesn't
// respond. The ESP32-S3's I2C peripheral goes through the chip's internal
// GPIO matrix (unlike, say, the LoRa radio's SPI pins, which are hardwired
// chip-to-chip) so a second bus can live on any free GPIO pair — GPIO1/2
// were cross-checked against every other pin already in use on this board
// (see SD_*_PIN's own comment above and greenpower_sender/CLAUDE.md) and
// are clean. Uses the ESP32's second hardware I2C controller (TwoWire
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

// ════════════════════════════════════════════════════════════════════
//  SENSOR READER — DS18B20 (GPIO6, 1-Wire digital)
// ════════════════════════════════════════════════════════════════════

// Raw Celsius reading from the last conversion, kept only for the serial
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                  GPS_RX_PIN, GPS_TX_PIN, GPS_BAUD);

    // ESC controller
    Serial2.begin(ESC_BAUD, SERIAL_8N1, ESC_RX_PIN, ESC_TX_PIN);
    Serial.printf("[OK]   ESC    Serial2  RX=%d TX=%d @ %d\n",
                  ESC_RX_PIN, ESC_TX_PIN, ESC_BAUD);

    // Enable external sensor power rail (GPIO36, active LOW) — Heltec V4
    pinMode(VEXT_CTRL, OUTPUT);
    digitalWrite(VEXT_CTRL, LOW);
    delay(500);                        // give rail plenty of time to stabilise
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    }

    // ⚠️ RTC temporarily DISABLED — not removed, just not called. Per
    // explicit request: GPIO2 (RTC_SCL_PIN) is needed for the Heltec V4
    // antenna front-end fix below (FEM_EN/CSD — see that section's own
    // comment for the full story: a -120dBm reading at 15ft traced to
    // this board's external antenna amplifier chip needing to be
    // explicitly enabled, which RadioLib has no way to know about).
    // Skipping initRtc() entirely means rtcWire.begin(RTC_SDA_PIN,
    // RTC_SCL_PIN) never runs, so GPIO2 is never claimed by I2C — safe to
    // reuse for FEM_EN without any pin conflict, and without needing to
    // desolder/move the RTC's physical wiring at all: `rtcReady` simply
    // stays false (its default), and getRtcTimestamp() already has a
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    // the live LoRa/dashboard telemetry is completely unaffected either
    // way, since epoch_time was already removed from the transmitted
    // packet in an earlier pass (see this file's own CLAUDE.md).
    // Re-enable by uncommenting the line below — but only once GPIO2 is
    // free again (i.e. the antenna fix moves to a different enable pin,
    // or is removed).
    // initRtc();
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
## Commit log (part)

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2026-05-01 attempting to fix ui
2026-05-01 fahhhhh
2026-05-05 fixed mock sender
2026-05-06 reworked display
    this is the most recent verison
2026-05-06 added required fonts to folder
2026-05-08 added the sender code and fixed other stuff
